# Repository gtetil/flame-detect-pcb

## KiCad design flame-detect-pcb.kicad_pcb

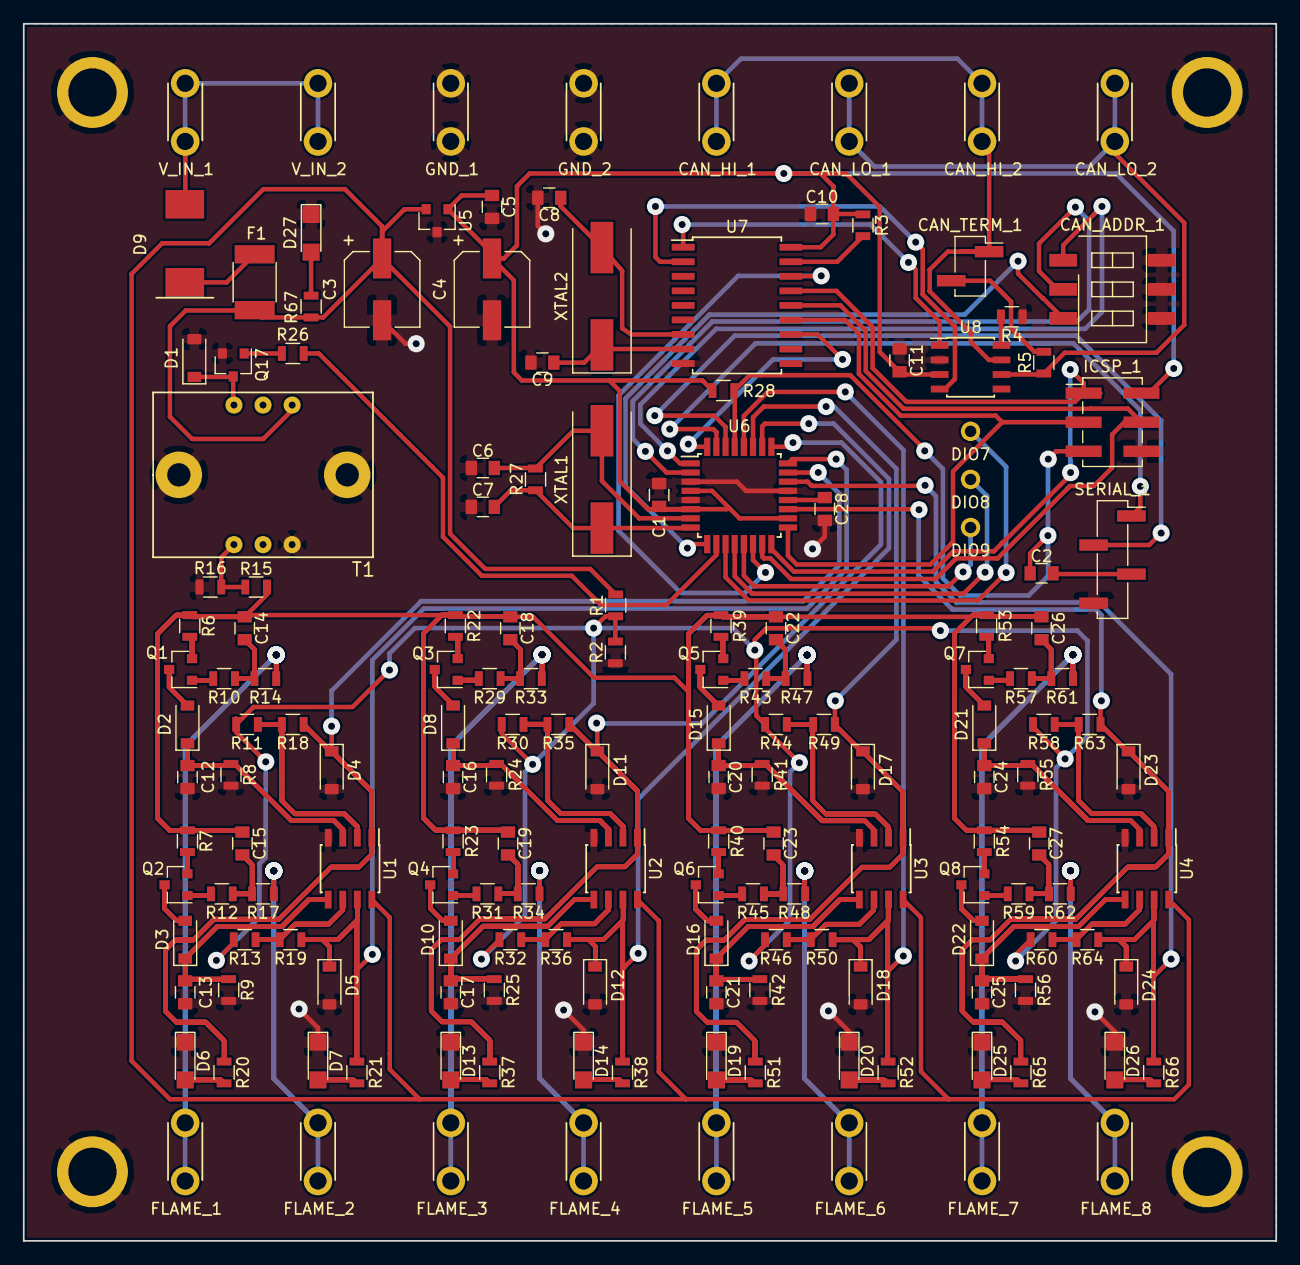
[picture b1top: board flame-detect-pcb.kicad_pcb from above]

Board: 2 copper layers, 109.4 x 106.3 mm, 170 parts (0 on the bottom side), 111 nets.

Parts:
C1, C2, C5, C10, C11, C28: 0.1uF; C_0805
C3, C4: 47uF; CP_Elec_6.3x5.3
C6, C7, C8, C9: 22pF; C_0805
C12, C13, C16, C17, C20, C21, C24, C25: 10nF; C_0805
C14, C15, C18, C19, C22, C23, C26, C27: 1nF; C_0805
CAN_ADDR_1: DIP_SW_3; SW_DIP_x3_W8.61mm_Slide_LowProfile
CAN_HI_1, CAN_HI_2: CONN_01X01; KEYSTONE_SPADE_TERM_(1287)
CAN_LO_1, CAN_LO_2: CONN_01X01; KEYSTONE_SPADE_TERM_(1287)
CAN_TERM_1: CONN_01X02; Pin_Header_Straight_1x02_Pitch2.54mm_SMD_Pin1Right
D1, D2, D3, D8, D10, D15, D16, D21, D22: BAV21W-7-F; D_SOD-123
D4, D5, D11, D12, D17, D18, D23, D24: BZT52C5V1-TP; D_SOD-123
D6, D7, D13, D14, D19, D20, D25, D26, D27: LED; LED_1206
D9: D_Schottky; DO-214AB
DIO7, DIO8, DIO9: CONN_01X01; SPARE_THROUGH_HOLE
F1: Polyfuse; R_1812
FLAME_1, FLAME_2, FLAME_3, FLAME_4, FLAME_5, FLAME_6, FLAME_7, FLAME_8: CONN_01X01; KEYSTONE_SPADE_TERM_(1287)
GND_1, GND_2: CONN_01X01; KEYSTONE_SPADE_TERM_(1287)
GND_3, GND_4, GND_5, GND_6: CONN_01X01; PEM_STANDOFF_THRU_(SMTSOB-116-12ET)
ICSP_1: CONN_02X03; Pin_Header_Straight_2x03_Pitch2.54mm_SMD
Q1, Q2, Q3, Q4, Q5, Q6, Q7, Q8: MMBT2907; SOT-23
Q17: MMBT2222; SOT-23
R1: 5.1K; R_0805
R2: 560R; R_0805
R3, R4, R18, R19, R35, R36, R49, R50, R63, R64: 10K; R_0805
R5: 120R; R_0805
R6, R7, R22, R23, R39, R40, R53, R54: 470K; R_0805
R8, R9, R24, R25, R41, R42, R55, R56: 5.1M; R_0805
R10, R12, R27, R29, R31, R43, R45, R57, R59: 1M; R_0805
R11, R13, R30, R32, R44, R46, R58, R60: 13K; R_0805
R14, R17, R33, R34, R47, R48, R61, R62: 3M; R_0805
R15: 10k; R_0805
R16: 10M; R_0805
R20, R21, R37, R38, R51, R52, R65, R66: 240R; R_0805
R26: 680R; R_0805
R28: 1k; R_0805
R67: 1K; R_0805
SERIAL_1: CONN_01X04; Pin_Header_Straight_1x04_Pitch2.54mm_SMD_Pin1Right
T1: TRANSFORMER_(42TL013-RC)
U1, U2, U3, U4: LM358; SOIC-8_3.9x4.9mm_Pitch1.27mm
U5: LM3480-5.0; SOT-23
U6: ATMEGA328P-AU; TQFP-32_7x7mm_Pitch0.8mm
U7: MCP2515T-I/SO; SOIC-18W_7.5x11.6mm_Pitch1.27mm
U8: MCP2551-I/SN; SOIC-8_3.9x4.9mm_Pitch1.27mm
V_IN_1, V_IN_2: CONN_01X01; KEYSTONE_SPADE_TERM_(1287)
XTAL1, XTAL2: Crystal; Crystal_SMD_HC49-SD

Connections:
5V: C1.1, C4.1, C5.1, C10.2, C11.2, ICSP_1.2, R3.1, R28.1, U5.1, U6.4, U6.6, U6.18, U7.18, U8.3
ADDR_0: CAN_ADDR_1.1, U6.1
ADDR_1: CAN_ADDR_1.2, U6.2
ADDR_2: CAN_ADDR_1.3, U6.9
AI0: D4.1, R18.1, R20.1, U1.1, U6.23
AI1: D5.1, R19.1, R21.1, U1.7, U6.24
AI2: D11.1, R35.1, R37.1, U2.1, U6.25
AI3: D12.1, R36.1, R38.1, U2.7, U6.26
AI4: D17.1, R49.1, R51.1, U3.1, U6.27
AI5: D18.1, R50.1, R52.1, U3.7, U6.28
AI6: D23.1, R63.1, R65.1, U4.1, U6.19
AI7: D24.1, R64.1, R66.1, U4.7, U6.22
GND: C1.2, C3.2, C4.2, C5.2, C6.1, C7.1, C8.2, C9.2, C10.1, C11.1, C12.2, C13.2, C16.2, C17.2, C20.2, C21.2, C24.2, C25.2, C28.2, CAN_ADDR_1.4, CAN_ADDR_1.5, CAN_ADDR_1.6, D1.2, D4.2, D5.2, D6.1, D7.1, D11.2, D12.2, D13.1, D14.1, D17.2, D18.2, D19.1, D20.1, D23.2, D24.2, D25.1, D26.1, D27.1, GND_1.1, GND_2.1, GND_3.1, GND_4.1, GND_5.1, GND_6.1, ICSP_1.6, Q17.2, R2.1, R4.1, R8.2, R9.2, R16.1, R24.2, R25.2, R41.2, R42.2, R55.2, R56.2, SERIAL_1.4, T1.3, T1.7, T1.8, U1.4, U2.4, U3.4, U4.4, U5.3, U6.3, U6.5, U6.21, U7.9, U8.2
INT: U6.32, U7.12
MISO: ICSP_1.1, U6.16, U7.15
MOSI: ICSP_1.4, U6.15, U7.14
unnamed: C2.2, SERIAL_1.3
unnamed: C6.2, R27.2, U6.7, XTAL1.2
unnamed: C7.2, R27.1, U6.8, XTAL1.1
unnamed: C8.1, U7.7, XTAL2.2
unnamed: C9.1, U7.8, XTAL2.1
unnamed: C12.1, D2.1, R8.1, U1.3
unnamed: C13.1, D3.1, R9.1, U1.5
unnamed: C14.2, R10.1, R14.2
unnamed: C15.2, R12.1, R17.2
unnamed: C16.1, D8.1, R24.1, U2.3
unnamed: C17.1, D10.1, R25.1, U2.5
unnamed: C18.2, R29.1, R33.2
unnamed: C19.2, R31.1, R34.2
unnamed: C20.1, D15.1, R41.1, U3.3
unnamed: C21.1, D16.1, R42.1, U3.5
unnamed: C22.2, R43.1, R47.2
unnamed: C23.2, R45.1, R48.2
unnamed: C24.1, D21.1, R55.1, U4.3
unnamed: C25.1, D22.1, R56.1, U4.5
unnamed: C26.2, R57.1, R61.2
unnamed: C27.2, R59.1, R62.2
unnamed: C28.1, U6.20
unnamed: CAN_HI_1.1, CAN_HI_2.1, CAN_TERM_1.1, U8.7
unnamed: CAN_LO_1.1, CAN_LO_2.1, R5.1, U8.6
unnamed: CAN_TERM_1.2, R5.2
unnamed: D1.1, Q17.3, T1.6
unnamed: D2.2, Q1.3
unnamed: D3.2, Q2.3
unnamed: D6.2, R20.2
unnamed: D7.2, R21.2
unnamed: D8.2, Q3.3
unnamed: D9.1, F1.2
unnamed: D9.2, V_IN_1.1, V_IN_2.1
unnamed: D10.2, Q4.3
unnamed: D13.2, R37.2
unnamed: D14.2, R38.2
unnamed: D15.2, Q5.3
unnamed: D16.2, Q6.3
unnamed: D19.2, R51.2
unnamed: D20.2, R52.2
unnamed: D21.2, Q7.3
unnamed: D22.2, Q8.3
unnamed: D25.2, R65.2
unnamed: D26.2, R66.2
unnamed: D27.2, R67.1
unnamed: DIO7.1, U6.11
unnamed: DIO8.1, U6.12
unnamed: DIO9.1, U6.13
unnamed: FLAME_1.1, R14.1
unnamed: FLAME_2.1, R17.1
unnamed: FLAME_3.1, R33.1
unnamed: FLAME_4.1, R34.1
unnamed: FLAME_5.1, R47.1
unnamed: FLAME_6.1, R48.1
unnamed: FLAME_7.1, R61.1
unnamed: FLAME_8.1, R62.1
unnamed: Q1.1, R10.2
unnamed: Q1.2, R6.2
unnamed: Q2.1, R12.2
unnamed: Q2.2, R7.2
unnamed: Q3.1, R29.2
unnamed: Q3.2, R22.2
unnamed: Q4.1, R31.2
unnamed: Q4.2, R23.2
unnamed: Q5.1, R43.2
unnamed: Q5.2, R39.2
unnamed: Q6.1, R45.2
unnamed: Q6.2, R40.2
unnamed: Q7.1, R57.2
unnamed: Q7.2, R53.2
unnamed: Q8.1, R59.2
unnamed: Q8.2, R54.2
unnamed: Q17.1, R26.1
unnamed: R3.2, U7.17
unnamed: R4.2, U8.8
unnamed: R11.1, R18.2, U1.2
unnamed: R13.1, R19.2, U1.6
unnamed: R15.1, R16.2, T1.1
unnamed: R26.2, U6.10
unnamed: R30.1, R35.2, U2.2
unnamed: R32.1, R36.2, U2.6
unnamed: R44.1, R49.2, U3.2
unnamed: R46.1, R50.2, U3.6
unnamed: R58.1, R63.2, U4.2
unnamed: R60.1, R64.2, U4.6
unnamed: U7.1, U8.1
unnamed: U7.2, U8.4
PULSE: C14.1, C15.1, C18.1, C19.1, C22.1, C23.1, C26.1, C27.1, R6.1, R7.1, R15.2, R22.1, R23.1, R39.1, R40.1, R53.1, R54.1
RST: C2.1, ICSP_1.5, R28.2, U6.29
RXD: SERIAL_1.2, U6.30
SCK: ICSP_1.3, U6.17, U7.13
SS: U6.14, U7.16
TXD: SERIAL_1.1, U6.31
VBATT: C3.1, F1.1, R1.2, R67.2, T1.4, U1.8, U2.8, U3.8, U4.8, U5.2
V_REF: R1.1, R2.2, R11.2, R13.2, R30.2, R32.2, R44.2, R46.2, R58.2, R60.2

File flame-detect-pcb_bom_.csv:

Component,Description,Part,References,Value,Footprint,Quantity Per PCB,Datasheet
1,Unpolarized capacitor,C,"C1, C2, C5, C10, C11",0.1uF,C_0805,5,
2,Unpolarized capacitor,C,"C12, C13, C16, C17, C20, C21, C24, C25",10nF,C_0805,8,
3,Unpolarized capacitor,C,"C14, C15, C18, C19, C22, C23, C26, C27",1nF,C_0805,8,
4,Unpolarized capacitor,C,"C6, C7, C8, C9",22pF,C_0805,4,
5,Polarised capacitor,CP,"C3, C4",47uF,C_0805,2,
6,"Connector, single row, 01x01, pin header",CONN_01X01,"CAN_HI1, CAN_LO1, DIO7, DIO8, DIO9, FLAME_1, FLAME_2, FLAME_3, FLAME_4, FLAME_5, FLAME_6, FLAME_7, FLAME_8, GND1, GND2, V_IN1, V_IN2",CONN_01X01,,17,
7,"Connector, single row, 01x02, pin header",CONN_01X02,CAN_TERM1,CONN_01X02,,1,
8,Diode,D,"D1, D2, D3, D8, D10, D15, D16, D21, D22",BAV21W-7-F,D_0805,9,
9,Zener Diode,D_Zener,"D4, D5, D11, D12, D17, D18, D23, D24",BZT52C5V1-TP,D_0805,8,https://en.wikipedia.org/wiki/Zener_diode
10,Schottky diode,D_Schottky,D9,D_Schottky,"SCHOTTKY_(PMEG3030EP,115)",1,
11,LED generic,LED,"D6, D7, D13, D14, D19, D20, D25, D26, D27",LED,,9,
12,"resettable fuse, polymeric positive temperature coefficient (PPTC)",Polyfuse,F1,Polyfuse,R_1812,1,
13,"Connector, double row, 02x03, pin header",CONN_02X03,ICSP1,CONN_02X03,,1,
14,Transistor NPN (general),Q_NPN_BEC,Q17,MMBT2222,SOT-23,1,
15,"40V Vce, 0.2A Ic, PNP, Small Signal Transistor, SOT-23",MMBT3906,"Q1, Q2, Q3, Q4, Q5, Q6, Q7, Q8",MMBT2907,SOT-23,8,http://www.nxp.com/documents/data_sheet/MMBT3906.pdf
16,Resistor,R,"R3, R4, R15",10K,R_0805,3,
17,Resistor,R,R16,10M,R_0805,1,
18,Resistor,R,R5,120R,R_0805,1,
19,Resistor,R,"R11, R13, R30, R32, R44, R46, R58, R60",13K,R_0805,8,
20,Resistor,R,"R10, R12, R18, R19, R27, R29, R31, R35, R36, R43, R45, R49, R50, R57, R59, R63, R64",1M,R_0805,17,
21,Resistor,R,"R28, R67",1k,R_0805,2,
22,Resistor,R,"R20, R21, R37, R38, R51, R52, R65, R66",240R,R_0805,8,
23,Resistor,R,"R14, R17, R33, R34, R47, R48, R61, R62",3M,R_0805,8,
24,Resistor,R,"R6, R7, R22, R23, R39, R40, R53, R54",470K,R_0805,8,
25,Resistor,R,R1,5.1K,R_0805,1,
26,Resistor,R,"R8, R9, R24, R25, R41, R42, R55, R56",5.1M,R_0805,8,
27,Resistor,R,R2,560R,R_0805,1,
28,Resistor,R,R26,680R,R_0805,1,
29,"Connector, single row, 01x04, pin header",CONN_01X04,SERIAL1,CONN_01X04,,1,
30,"Transformer, split primary, single secondary",TRANSFORMER_(42TL013-RC),T1,TRANSFORMER_(42TL013-RC),TRANSFORMER_(42TL013-RC),1,
31,"TQFP32, 16k Flash, 1kB SRAM, 512B EEPROM",ATMEGA328P-AU,U6,ATMEGA328P-AU,TQFP32,1,http://www.atmel.com/images/atmel-8271-8-bit-avr-microcontro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
32,,DIP_SW_3,U9,DIP_SW_3,,1,
33,"100mA, Quasi Low Dropout Voltage Regulator, 3.3V positive fixed output, SOT-23 package",LM3480-5.0,U5,LM3480-5.0,SOT-23,1,http://www.ti.com/lit/ds/symlink/lm3480.pdf
34,Dual Op amp (low power),LM358,"U1, U2, U3, U4",LM358,,4,ns/lm158.pdf
35,"Stand-Alone CAN Controller with SPI Interface, SOIC-18, Extended temperature range",MCP2515T-I/SO,U7,MCP2515T-I/SO,,1,http://ww1.microchip.com/downloads/en/DeviceDoc/21801e.pdf
36,"High-Speed CAN Transceiver, 1Mbps, 5V supply, SOIC8 package",MCP2551-I/SN,U8,MCP2551-I/SN,SOIC-8_3.9x4.9mm_Pitch1.27mm,1,http://ww1.microchip.com/downloads/en/devicedoc/21667d.pdf
37,Two pin crystal,Crystal,"XTAL1, XTAL2",Crystal,,2,





Component Groups:,37
Component Count:,163
Fitted Components:,163
Number of PCBs:,1
Total components:,163
Schematic Version:,
Schematic Date:,
BoM Date:,3/19/2018 12:58:17 PM
Schematic Source:,C:\Users\gtetil\Documents\Projects\flame-detect-pcb\flame-detect-pcb.sch
KiCad Version:,Eeschema 4.0.6

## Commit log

2017-10-29 - Initial commit.
2017-10-29 - Created transformer block and footprint.
2017-10-30 - Created circuits and footprints.
2017-10-31 - Finished board layout.
2017-11-01 - Created gerbers, cam, and lmd files.
2017-11-01 - Recreated. Was missing drill file.
2018-03-19 - Finished circuit for new 8 channel version. Ready to start on PCB.
2018-03-19 - Finished footprints.
2018-03-20 - Finished PCB layout.
2018-03-21 - Fixed a couple layout issues, then created gerbers.
2018-03-24 - Created LPKF files.
2018-03-28 - Fixed several bugs.
2018-04-04 - Changed transformer transistor resistor to 10kohm.
